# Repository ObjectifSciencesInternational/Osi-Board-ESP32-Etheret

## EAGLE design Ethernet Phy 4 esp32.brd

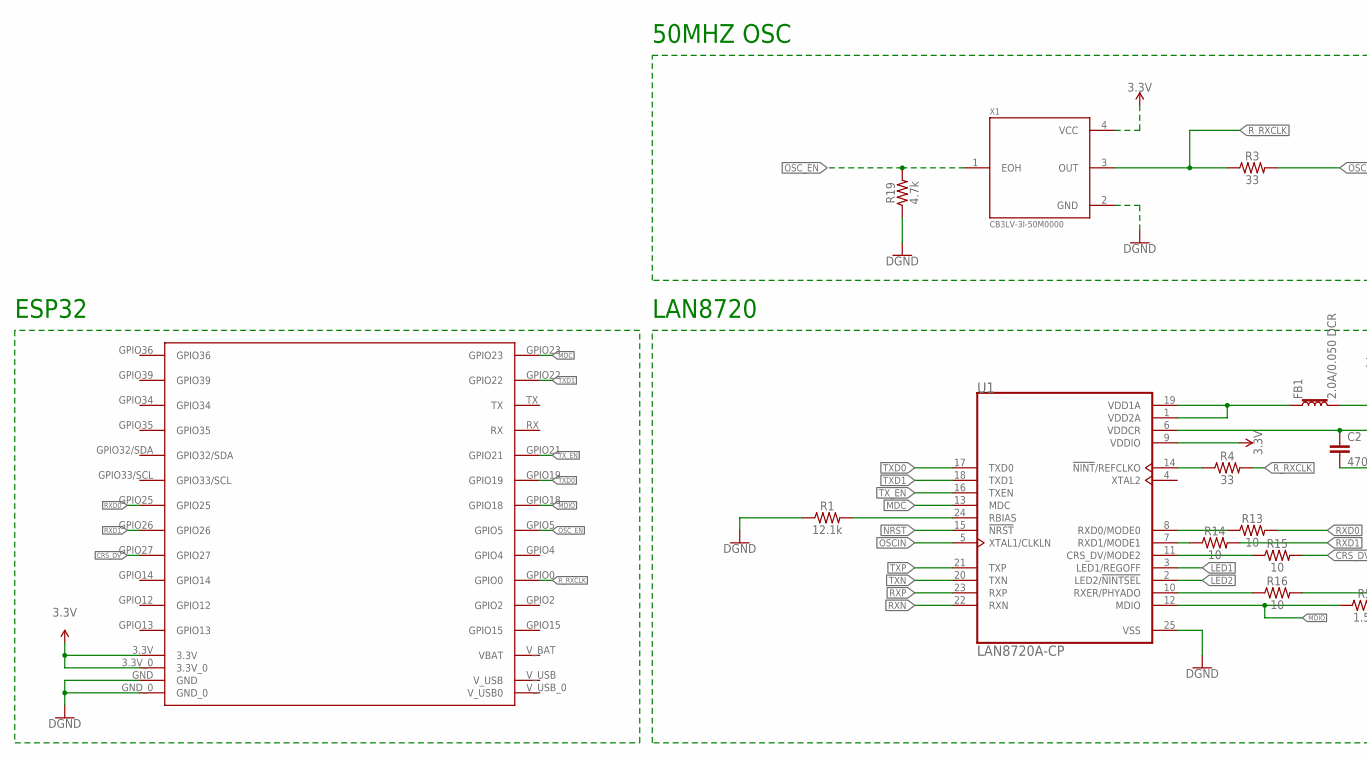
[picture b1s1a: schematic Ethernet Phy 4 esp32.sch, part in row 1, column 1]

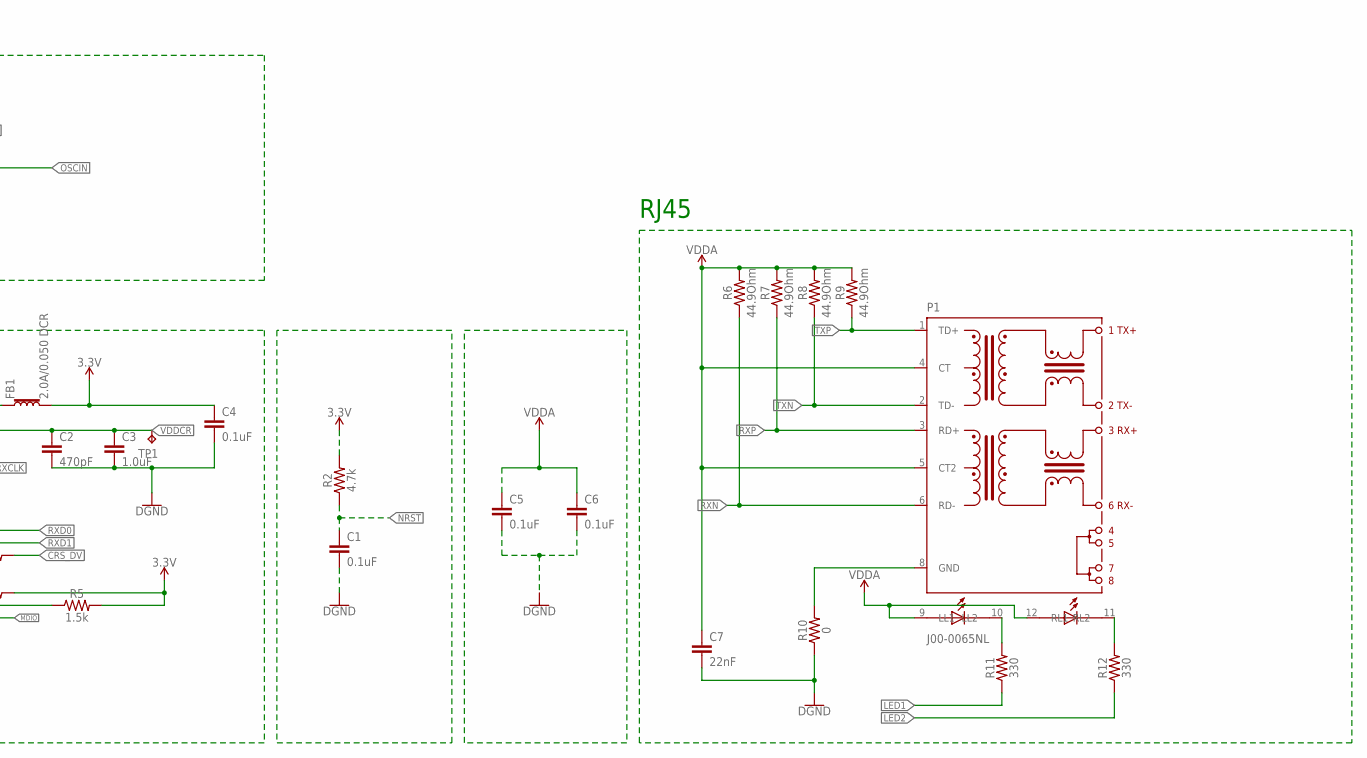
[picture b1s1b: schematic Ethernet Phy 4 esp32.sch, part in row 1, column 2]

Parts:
C1, C4, C5, C6: 0.1uF; 0603
C2: 470pF; 0603
C3: 1.0uF; 0603
C7: 22nF; 0603
FB1: 2.0A/0.050 DCR; 0603
P1: J00-0065NL; PULSE_J00-0065NL
R1: 12.1k; 0603
R2, R19: 4.7k; 0603
R3, R4: 33; 0603
R5: 1.5k; 0603
R6, R7, R8, R9: 44.9Ohm; 0603
R10: 0; 0603
R11, R12: 330; 0603
R13, R14, R15, R16: 10; 0603
TP1: TPB1,27; B1,27
U1: LAN8720A-CP; QFN50P400X400X100-25N
U$4: OSIBOARD
X1: CB3LV-3I-50M0000; OSCCC700X500X180-4N

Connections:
3.3V: C4.1, FB1.2, R2.2, R5.2, R16.2, U1.9 (VDDIO), U$4.3.3V, U$4.3.3V_0, X1.4 (VCC)
CRS_DV: R15.2, U$4.GPIO27
GND: C1.2, C2.2, C3.2, C4.2, C5.2, C6.2, C7.2, R1.1, R10.1, R19.1, U1.25 (VSS), U$4.GND, U$4.GND_0, X1.2 (GND)
LED1: R11.1, U1.3 (LED1/REGOFF)
LED2: R12.1, U1.2 (LED2/!NINTSEL!)
MDC: U1.13 (MDC), U$4.GPIO23
MDIO: R5.1, U1.12 (MDIO), U$4.GPIO18
unnamed: R1.2, U1.24 (RBIAS)
unnamed: R4.1, U1.14 (!NINT!/REFCLKO)
unnamed: FB1.1, U1.1 (VDD2A), U1.19 (VDD1A)
unnamed: P1.10 (LL2), R11.2
unnamed: P1.8 (GND), R10.2
unnamed: P1.11 (RL2), R12.2
unnamed: R14.1, U1.7 (RXD1/MODE1)
unnamed: R13.1, U1.8 (RXD0/MODE0)
unnamed: R15.1, U1.11 (CRS_DV/MODE2)
unnamed: R16.1, U1.10 (RXER/PHYADO)
NRST: C1.1, R2.1, U1.15 (!NRST)
OSCIN: R3.2, U1.5 (XTAL1/CLKLN)
OSC_EN: R19.2, U$4.GPIO5, X1.1 (EOH)
RXD0: R13.2, U$4.GPIO25
RXD1: R14.2, U$4.GPIO26
RXN: P1.6 (RD-), R6.1, U1.22 (RXN)
RXP: P1.3 (RD+), R7.1, U1.23 (RXP)
R_RXCLK: R3.1, R4.2, U$4.GPIO0, X1.3 (OUT)
TXD0: U1.17 (TXD0), U$4.GPIO19
TXD1: U1.18 (TXD1), U$4.GPIO22
TXN: P1.2 (TD-), R8.1, U1.20 (TXN)
TXP: P1.1 (TD+), R9.1, U1.21 (TXP)
TX_EN: U1.16 (TXEN), U$4.GPIO21
VDDA: C5.1, C6.1, C7.1, P1.4 (CT), P1.5 (CT2), P1.9 (LL1), P1.12 (RL1), R6.2, R7.2, R8.2, R9.2
VDDCR: C2.1, C3.1, TP1.TP, U1.6 (VDDCR)

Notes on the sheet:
LAN8720
50MHZ OSC
RJ45
ESP32

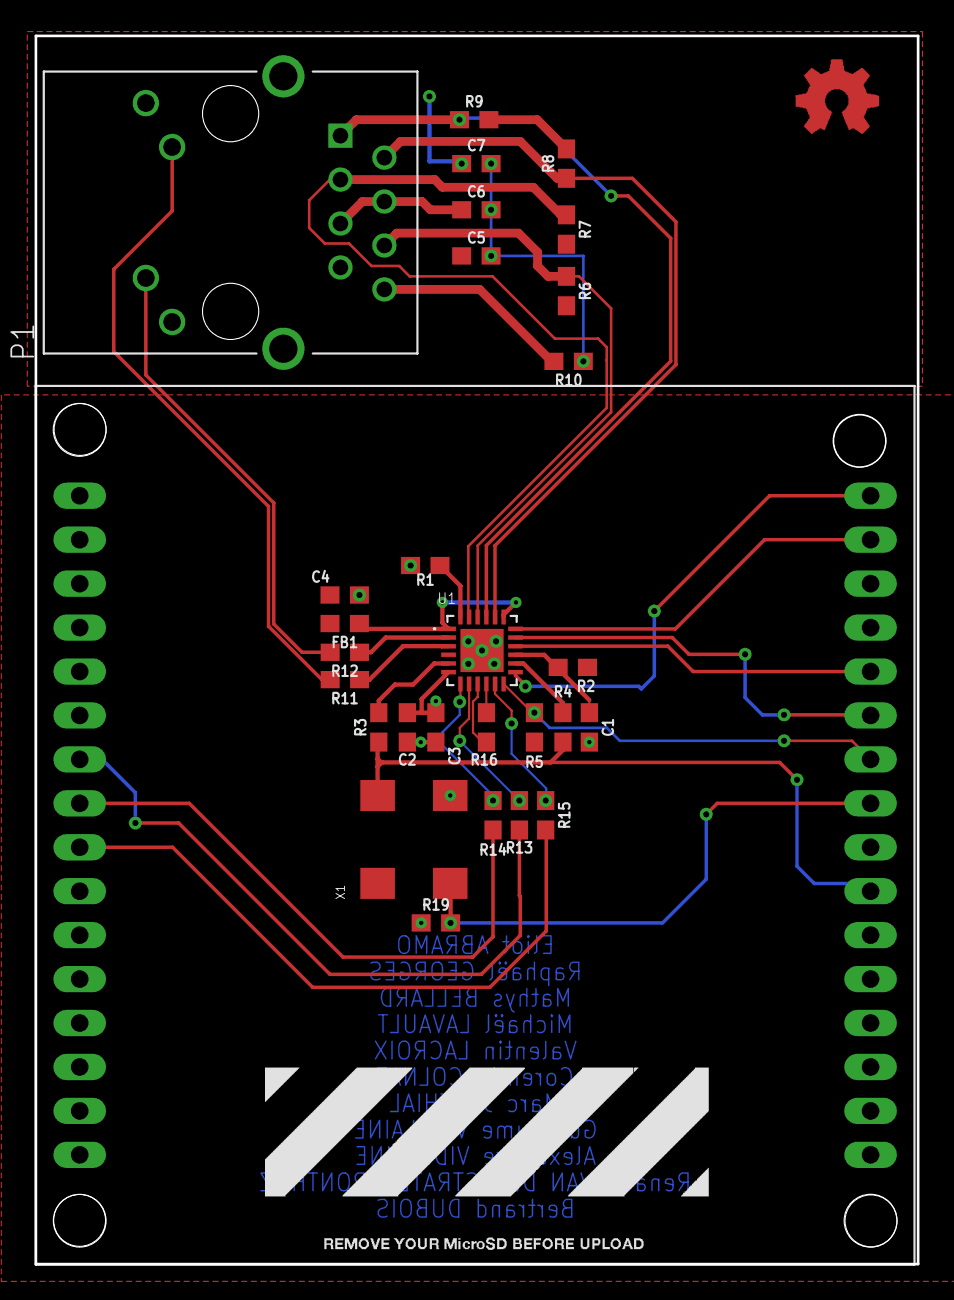
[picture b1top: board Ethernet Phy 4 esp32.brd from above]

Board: 2 copper layers, 51.0 x 71.0 mm, 30 parts (1 on the bottom side), 32 nets.

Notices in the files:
parts and their libraries:
SparkFun-Resistors: Licensing: Creative Commons ShareAlike 4.0 International - https://creativecommons.org/licenses/by-sa/4.0
